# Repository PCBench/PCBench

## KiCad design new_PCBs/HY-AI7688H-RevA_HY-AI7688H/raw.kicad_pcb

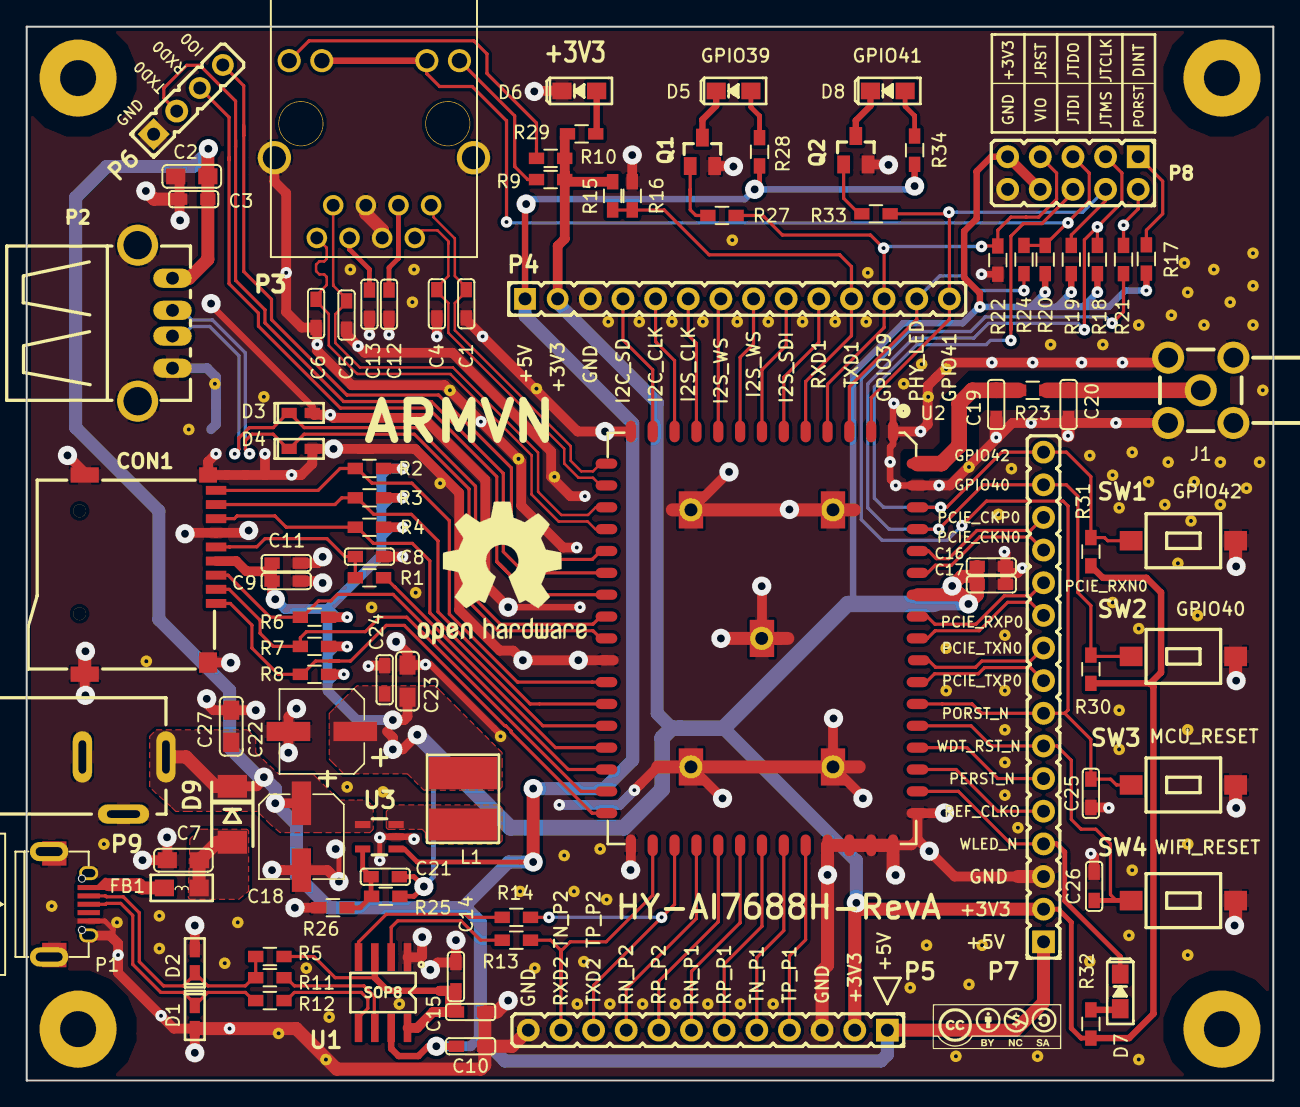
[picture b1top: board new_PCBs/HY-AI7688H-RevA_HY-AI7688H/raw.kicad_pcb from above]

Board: 2 copper layers, 97.0 x 82.0 mm, 96 parts (0 on the bottom side), 80 nets.

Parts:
C1, C4, C5, C6, C19, C20: DNP; CAPC0603x018M
C2, C7, C27: 10uF; CAPC0805X024M
C3, C10, C11, C12, C13, C14, C15, C17, C21, C24, C25, C26: 100nF; CAPC0603x018M
C8, C9: NC; CAPC0603x018M
C16: 100uF; CAPC0603x018M
C18, C22: 220uF/16V; CAPAE_6.3x7.7-M
C23: 22uF; CAPC0805X024M
CON1: TF-Micro-SDCard; TFC-WPAPR-08
D1, D2, D3, D4: TVS; DIOC_0603X018
D5, D6, D7, D8: LED; LED_0805x024M
D9: D_SS24; DO-214AA
FB1: FBM0805PT800S; FB0805x034M
J1: CONN_SMA; MOLEX_0731000114
L1: CDRH4D22; INDC5050X24M
MH1, MH2, MH3, MH4: MH_32.8MM; Mounting_hole_2.8mm
P1: USB_OTG; USB_Micro-B_DGK609-4048-1-ND
P2: USB_A; USB_A_H_PTH
P3: HR911102A
P4: CONN_01X14; HDRV14W64_1X14_3556X254X1154
P5: CONN_01X12; HDRV12W64_1X12_3048X254X1154
P6: CONN_01X04; HDRV4W64_1X4_1016X254X1154
P7: CONN_01X16; HDRV16W64_1X16_4046X254X1154
P8: CONN_02X05; HDRV10W64P254_2X5_1270X254X115P
P9: CONN-PWR-JACK; CONN_PWR_JACK_25
Q1, Q2: LMBT3904; SOT23-3-MMBT3904-M
R1, R13, R14, R21, R24: 22R; RESC0603x018M
R2, R3, R4, R6, R7, R8, R17, R30, R31: 10K; RESC0603x018M
R5: 1.5K; RESC0603x018M
R9, R10, R32: 330R; RESC0603x018M
R11, R12: 27R; RESC0603x018M
R15: 4.7K; RESC0603x018M
R16: DNP; RESC0603x018M
R18, R19, R20, R22: 1K; RESC0603x018M
R23: 0R; RESC0603x018M
R25: 47K_1%; RESC0603x018M
R26: 10.5K_1%; RESC0603x018M
R27, R33: 2.2K; RESC0603x018M
R28, R29, R34: 560R; RESC0603x018M
SW1: SW_USR1; SW-T1107A(6x3,8x2,5MM)
SW2: SW_USR2; SW-T1107A(6x3,8x2,5MM)
SW3: MPU_RESET; SW-T1107A(6x3,8x2,5MM)
SW4: WIFI_RESET; SW-T1107A(6x3,8x2,5MM)
U1: PL2303SA; SOP127P600x155-8-M
U2: AI7688H; AI7688H-M
U3: SY8008; SOT-23-5

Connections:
+3V3: C9.2, C11.2, C16.2, C17.2, C21.2, C22.1, C23.2, C24.2, CON1.4, L1.2, P4.2, P5.2, P7.2, P8.8, P8.9, R2.2, R3.2, R4.2, R6.2, R7.2, R8.2, R9.1, R10.1, R15.2, R17.2, R18.2, R19.2, R20.2, R25.2, R29.2, R30.2, R31.2, R32.1, U2.54
+5V: C2.2, C3.2, C10.2, C18.1, C27.2, D9.1, P2.1, P4.1, P5.1, P7.1, P9.1, R28.2, R34.2, U1.7, U3.1, U3.4
+5V_USBOTG: C7.2, D9.2, FB1.2
/AI7688H/D+: R12.1, U1.5
/AI7688H/D-: R11.1, U1.6
/AI7688H/EJTAG_DINT: P8.1, R17.1
/AI7688H/EJTAG_PORST_N: P8.2, R21.1
/AI7688H/EPHY_LED0_N: P3.10, P3.11, P8.5, R20.1, R24.2
/AI7688H/GPIO_0: P6.4, U2.18
/AI7688H/I2C_SCLK: P4.5, U2.11
/AI7688H/I2C_SD: P4.4, U2.12
/AI7688H/I2S_SCLK: P4.6, U2.10
/AI7688H/I2S_SDI: P4.9, U2.7
/AI7688H/I2S_SDO: P4.8, U2.8
/AI7688H/I2S_WS: P4.7, U2.9
/AI7688H/JRST_GPIO_39: P4.12, P8.7, R22.2, R27.1, U2.4
/AI7688H/JTCLK_GPIO_40: P7.15, P8.3, R18.1, R30.1, SW2.1, U2.57
/AI7688H/JTDI_GPIO_42: P7.16, P8.6, R31.1, SW1.1, U2.58
/AI7688H/JTDO_EPHY_LED0_N: P4.13, R24.1, U2.3
/AI7688H/JTMS_GPIO_41: P4.14, P8.4, R19.1, R33.1, U2.2
/AI7688H/MDI_P0_R_N: C4.2, P3.2, U2.15
/AI7688H/MDI_P0_R_P: C1.2, P3.1, U2.14
/AI7688H/MDI_P0_T_N: C6.2, P3.8, U2.17
/AI7688H/MDI_P0_T_P: C5.2, P3.7, U2.16
/AI7688H/MDI_RN_P1: P5.7, U2.36
/AI7688H/MDI_RN_P2: P5.9, U2.34
/AI7688H/MDI_RN_P3: CON1.7, R4.1, U2.26
/AI7688H/MDI_RN_P4: CON1.3, R6.1, U2.28
/AI7688H/MDI_RP_P1: P5.6, U2.37
/AI7688H/MDI_RP_P2: P5.8, U2.35
/AI7688H/MDI_RP_P3: CON1.8, R3.1, U2.25
/AI7688H/MDI_RP_P4: R1.1, U2.27
/AI7688H/MDI_TN_P1: P5.5, U2.38
/AI7688H/MDI_TN_P2: P5.11, R13.1, U2.32
/AI7688H/MDI_TN_P3: CON1.9, R2.1, U2.24
/AI7688H/MDI_TN_P4: CON1.1, R8.1, U2.30
/AI7688H/MDI_TP_P1: P5.4, U2.39
/AI7688H/MDI_TP_P2: P5.10, R14.1, U2.33
/AI7688H/MDI_TP_P4: CON1.2, R7.1, U2.29
/AI7688H/PCIE_CK0_N: P7.13, U2.55
/AI7688H/PCIE_CK0_P: P7.14, U2.56
/AI7688H/PCIE_RX0_N: P7.12, U2.53
/AI7688H/PCIE_RX0_P: P7.11, U2.52
/AI7688H/PCIE_TX0_N: P7.10, U2.51
/AI7688H/PCIE_TX0_P: P7.9, U2.50
/AI7688H/PERST_N: P7.6, U2.47
/AI7688H/PORST_N: C25.1, P7.8, R21.2, SW3.1, U2.49
/AI7688H/REF_CLKO: P7.5, U2.46
/AI7688H/RF: C19.2, R23.2, U2.60
/AI7688H/UART_7688_RXD0: P6.3, U2.20
/AI7688H/UART_7688_RXD1: P4.10, U2.6
/AI7688H/UART_7688_TXD0: P6.2, U2.19
/AI7688H/UART_7688_TXD1: P4.11, R15.1, R16.2, U2.5
/AI7688H/USB_D_N: D4.1, P2.2, U2.22
/AI7688H/USB_D_P: D3.1, P2.3, U2.21
/AI7688H/USB_OTG_D+: D1.1, P1.3, R12.2
/AI7688H/USB_OTG_D-: D2.1, P1.2, R5.1, R11.2
/AI7688H/WDT_RST_N: C26.1, P7.7, SW4.1, U2.48
/AI7688H/WLED_N: D7.1, P7.4, U2.45
GND: C1.1, C2.1, C3.1, C4.1, C5.1, C6.1, C7.1, C8.1, C9.1, C10.1, C11.1, C12.1, C13.1, C14.1, C15.1, C16.1, C17.1, C18.2, C19.1, C20.1, C22.2, C23.1, C24.1, C25.2, C26.2, C27.1, CON1.6, CON1.10, CON1.11, CON1.12, CON1.13, D1.2, D2.2, D3.2, D4.2, D6.1, J1.2, J1.3, J1.4, J1.5, P1.5, P1.6, P2.4, P2.5, P3.4, P3.5, P3.13, P3.14, P4.3, P5.3, P5.12, P6.1, P7.3, P8.10, P9.2, P9.3, Q1.2, Q2.2, R16.1, R22.1, R26.1, SW1.2, SW2.2, SW3.2, SW4.2, U1.1, U2.1, U2.13, U2.23, U2.31, U2.40, U2.41, U2.42, U2.43, U2.44, U2.59, U2.61, U2.62, U2.63, U2.64, U2.65, U3.2
unnamed: C8.2, CON1.5, R1.2
unnamed: C12.2, P3.3
unnamed: C13.2, P3.6
unnamed: C20.2, J1.1, R23.1
unnamed: C21.1, R25.1, R26.2, U3.5
unnamed: D5.1, Q1.3
unnamed: D5.2, R28.1
unnamed: D6.2, R29.1
unnamed: D7.2, R32.2
unnamed: D8.1, Q2.3
unnamed: D8.2, R34.1
unnamed: FB1.1, P1.1
unnamed: L1.1, U3.3
unnamed: P3.9, R9.2
unnamed: P3.12, R10.2
unnamed: Q1.1, R27.2
unnamed: Q2.1, R33.2
unnamed: R13.2, U1.2
unnamed: R14.2, U1.4
VO_3V3: C14.2, C15.2, R5.2, U1.3, U1.8

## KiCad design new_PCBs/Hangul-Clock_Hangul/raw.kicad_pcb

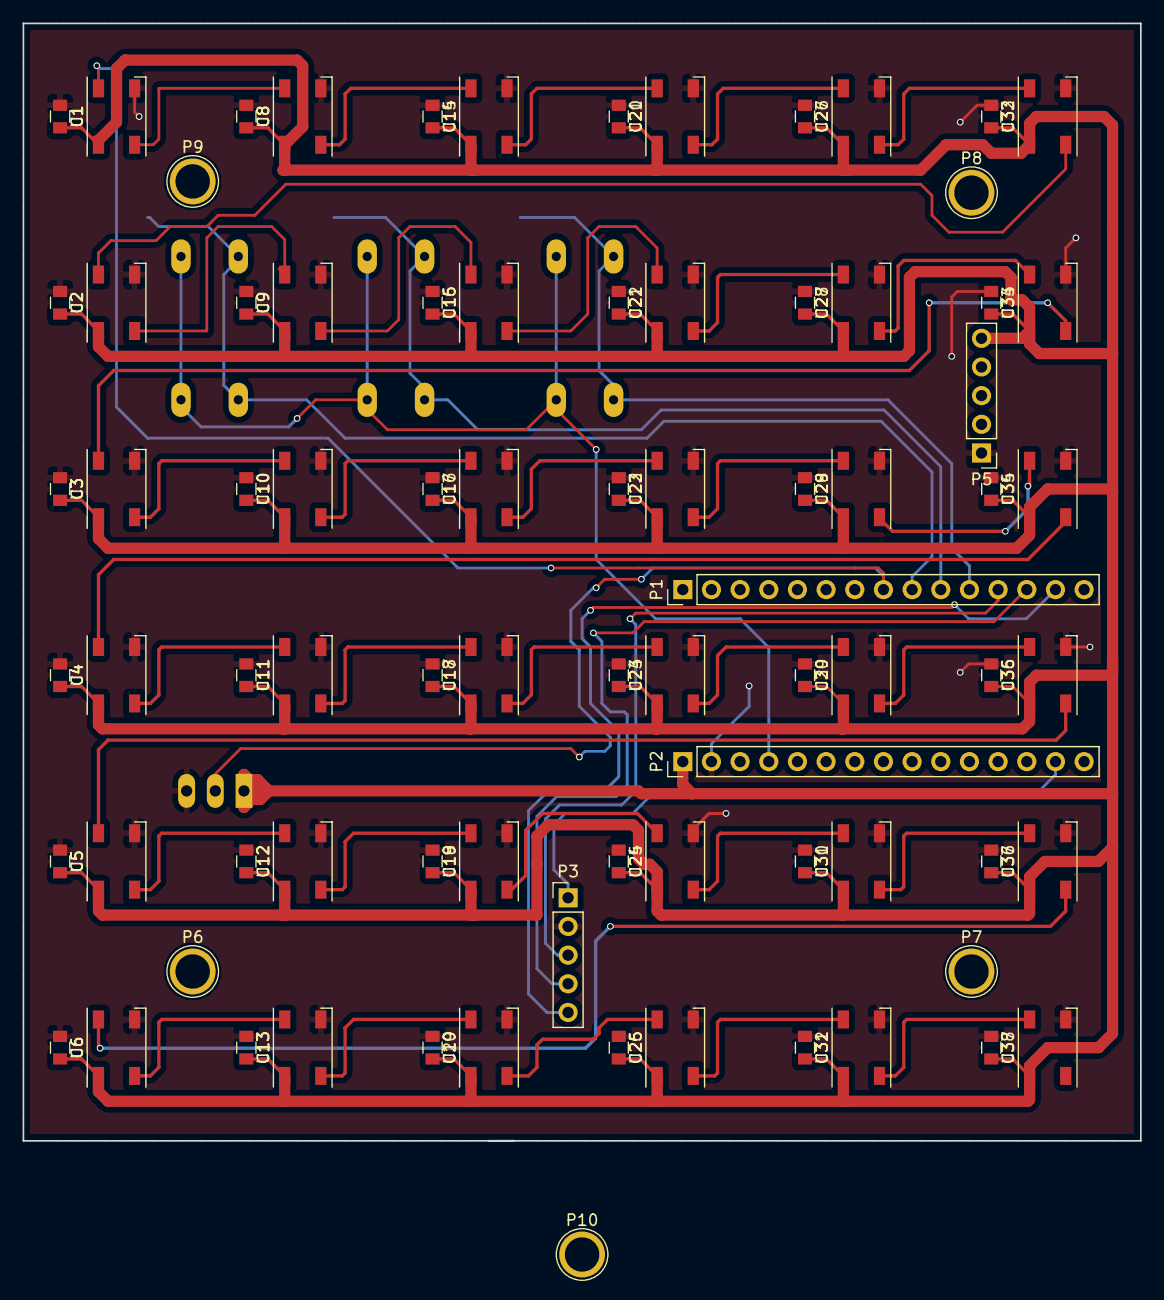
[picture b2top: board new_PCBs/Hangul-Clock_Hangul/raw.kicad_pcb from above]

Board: 2 copper layers, 99.0 x 99.0 mm, 88 parts (0 on the bottom side), 46 nets.

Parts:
C1, C2, C3, C4, C5, C6, C8, C9, C10, C11, C12, C13, C15, C16, C17, C18, C19, C20, C21, C22, C23, C24, C25, C26, C27, C28, C29, C30, C31, C32, C33, C34, C35, C36, C37, C38: C; C_0805
P1: NANO_1; Pin_Header_Straight_1x15_Pitch2.54mm
P2: NANO_2; Pin_Header_Straight_1x15_Pitch2.54mm
P3: DS1302; Pin_Header_Straight_1x05_Pitch2.54mm
P4: CONN_01X03; MOLEX-5045-03A
P5: POWER; Pin_Header_Straight_1x05_Pitch2.54mm
P6, P7, P8, P9: S; 1pin
P10: s; 1pin
R1, R2, R3: R; R_0805BCU
SW1: SW_R; SW_PUSH-12mmBCU
SW2: SW_G; SW_PUSH-12mmBCU
SW3: SW_B; SW_PUSH-12mmBCU
U1, U2, U3, U4, U5, U6, U8, U9, U10, U11, U12, U13, U14, U15, U16, U17, U18, U19, U20, U21, U22, U23, U24, U25, U26, U27, U28, U29, U30, U31, U32, U33, U34, U35, U36, U37: WS2812B; LED_WS2812B-PLCC4

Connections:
+5V: P2.4, SW1.1, SW2.1, SW3.1
+5VA: C1.2, C2.2, C3.2, C4.2, C5.2, C6.2, C8.2, C9.2, C10.2, C11.2, C12.2, C13.2, C15.2, C16.2, C17.2, C18.2, C19.2, C20.2, C21.2, C22.2, C23.2, C24.2, C25.2, C26.2, C27.2, C28.2, C29.2, C30.2, C31.2, C32.2, C33.2, C34.2, C35.2, C36.2, C37.2, C38.2, P2.1, P4.1, P5.5, U1.1, U2.1, U3.1, U4.1, U5.1, U6.1, U8.1, U9.1, U10.1, U11.1, U12.1, U13.1, U14.1, U15.1, U16.1, U17.1, U18.1, U19.1, U20.1, U21.1, U22.1, U23.1, U24.1, U25.1, U26.1, U27.1, U28.1, U29.1, U30.1, U31.1, U32.1, U33.1, U34.1, U35.1, U36.1, U37.1
CLK: P1.12, P3.3
DAT: P1.13, P3.4
DIN: P1.8, P4.2, U1.4
GND: C1.1, C2.1, C3.1, C4.1, C5.1, C6.1, C8.1, C9.1, C10.1, C11.1, C12.1, C13.1, C15.1, C16.1, C17.1, C18.1, C19.1, C20.1, C21.1, C22.1, C23.1, C24.1, C25.1, C26.1, C27.1, C28.1, C29.1, C30.1, C31.1, C32.1, C33.1, C34.1, C35.1, C36.1, C37.1, C38.1, P1.4, P2.2, P3.2, P4.3, P5.1, R1.1, R2.1, R3.1, U1.3, U2.3, U3.3, U4.3, U5.3, U6.3, U8.3, U9.3, U10.3, U11.3, U12.3, U13.3, U14.3, U15.3, U16.3, U17.3, U18.3, U19.3, U20.3, U21.3, U22.3, U23.3, U24.3, U25.3, U26.3, U27.3, U28.3, U29.3, U30.3, U31.3, U32.3, U33.3, U34.3, U35.3, U36.3, U37.3
unnamed: P1.9, R1.2, SW1.2
unnamed: P1.10, R2.2, SW2.2
unnamed: P1.11, R3.2, SW3.2
unnamed: P2.14, P3.1
unnamed: U1.2, U8.4
unnamed: U2.2, U9.4
unnamed: U2.4, U32.2
unnamed: U3.4, U33.2
unnamed: U10.2, U16.4
unnamed: U3.2, U10.4
unnamed: U11.2, U17.4
unnamed: U4.2, U11.4
unnamed: U12.2, U18.4
unnamed: U5.2, U12.4
unnamed: U13.2, U19.4
unnamed: U6.2, U13.4
unnamed: U14.2, U20.4
unnamed: U8.2, U14.4
unnamed: U15.2, U21.4
unnamed: U9.2, U15.4
unnamed: U16.2, U22.4
unnamed: U17.2, U23.4
unnamed: U18.2, U24.4
unnamed: U19.2, U25.4
unnamed: U20.2, U26.4
unnamed: U21.2, U27.4
unnamed: U22.2, U28.4
unnamed: U23.2, U29.4
unnamed: U24.2, U30.4
unnamed: U25.2, U31.4
unnamed: U26.2, U32.4
unnamed: U27.2, U33.4
unnamed: U28.2, U34.4
unnamed: U29.2, U35.4
unnamed: U30.2, U36.4
unnamed: U31.2, U37.4
unnamed: U4.4, U34.2
unnamed: U5.4, U35.2
unnamed: U6.4, U36.2
RST: P1.14, P3.5

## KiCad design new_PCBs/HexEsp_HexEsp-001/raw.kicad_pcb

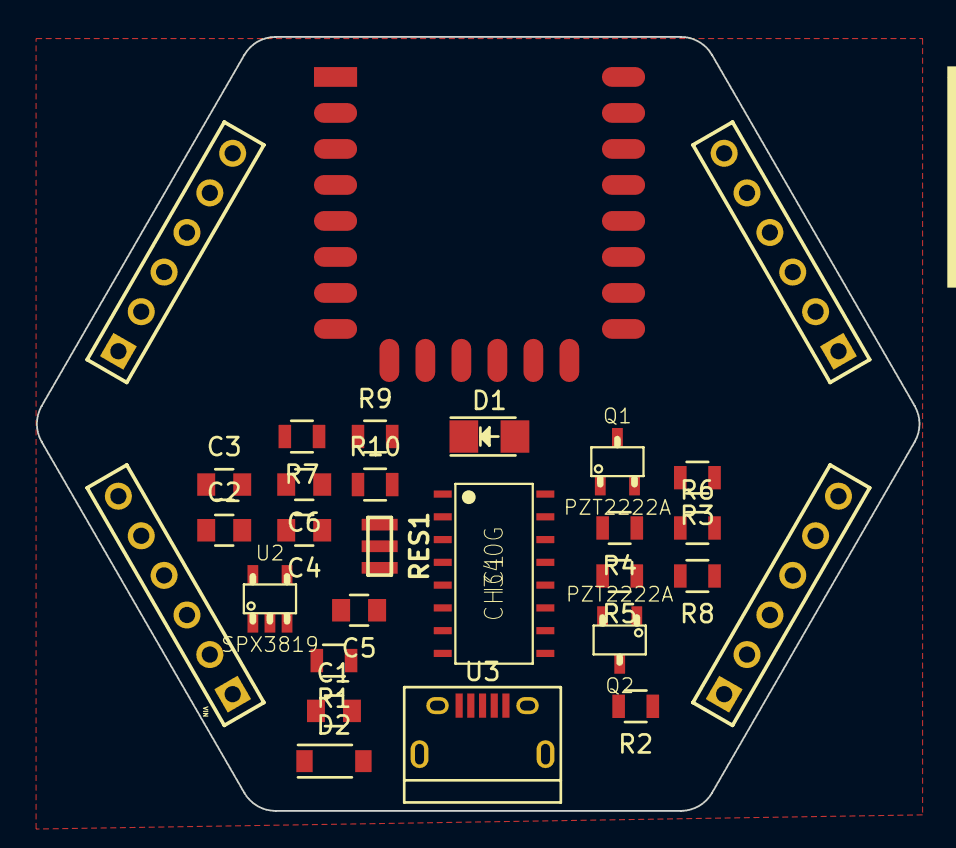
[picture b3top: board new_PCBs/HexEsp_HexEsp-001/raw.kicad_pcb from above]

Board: 2 copper layers, 49.0 x 43.0 mm, 29 parts (0 on the bottom side), 30 nets.

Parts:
C1, C2, C4: 10uF; C_0805
C3: 1uF; C_0805
C5, C6: 100nF; C_0805
D1: PURPLE; LED_1206
D2: MBR120; SOD-123
IC1: CH340G; SOP-16
J1, J2, J3, J4: 1x6_female_pin_Header_2.54mm; 1x6-Socket-header-2.54mm
Q1, Q2: PZT2222A; AB2_SOT23-3
R1, R2, R4, R5: 10K; R_0805
R3, R6, R7, R8: 1K; R_0805
R9, R10: 470; R_0805
RES1: AB2_RES_3P; murata-resonator_SMD_CSTCE8M00G55-R0
U1: ESP-12E
U2: SPX3819; AB2_SOT23-5
U3: MICRO-B_USB; USB_Micro-B

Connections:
+3V3: C2.1, C3.1, D1.2, J2.2, J4.4, R2.1, R6.2, R7.2, U1.8, U2.5
/ADC: J1.5, U1.2
/CH_PD: J1.4, R7.1, U1.3
/D+: IC1.5, U3.3
/D-: IC1.6, U3.2
/DTR: IC1.13, Q1.3, R5.2
/EN: R1.2, U2.3
/GPIO0: J3.2, Q1.2, R3.1, U1.18
/GPIO2: J3.1, R6.1, U1.17
/GPIO4: J3.3, U1.19
/GPIO5: J3.4, U1.20
/GPIO12: J2.5, U1.6
/GPIO13: J2.4, U1.7
/GPIO14: J2.6, U1.5
/GPIO15: J4.6, R8.2, U1.16
/GPIO16: J1.3, U1.4
/RESET: J1.6, Q2.2, R2.2, U1.1
/RTS: IC1.14, Q2.3, R4.2
/RXD: J3.5, R9.1, U1.21
/TXD: J3.6, R10.1, U1.22
/XI: IC1.7, RES1.1
/XO: IC1.8, RES1.3
GND: C1.2, C2.2, C3.2, C4.2, C5.2, C6.2, IC1.1, J2.3, J4.5, R8.1, RES1.2, U1.15, U2.2, U3.5
unnamed: C5.1, IC1.4
unnamed: D1.1, R3.2
unnamed: IC1.2, R9.2
unnamed: IC1.3, R10.2
unnamed: Q1.1, R4.1
unnamed: Q2.1, R5.1
VBUS: C1.1, C4.1, C6.1, D2.1, D2.2, IC1.16, J2.1, J4.1, R1.1, U2.1, U3.1

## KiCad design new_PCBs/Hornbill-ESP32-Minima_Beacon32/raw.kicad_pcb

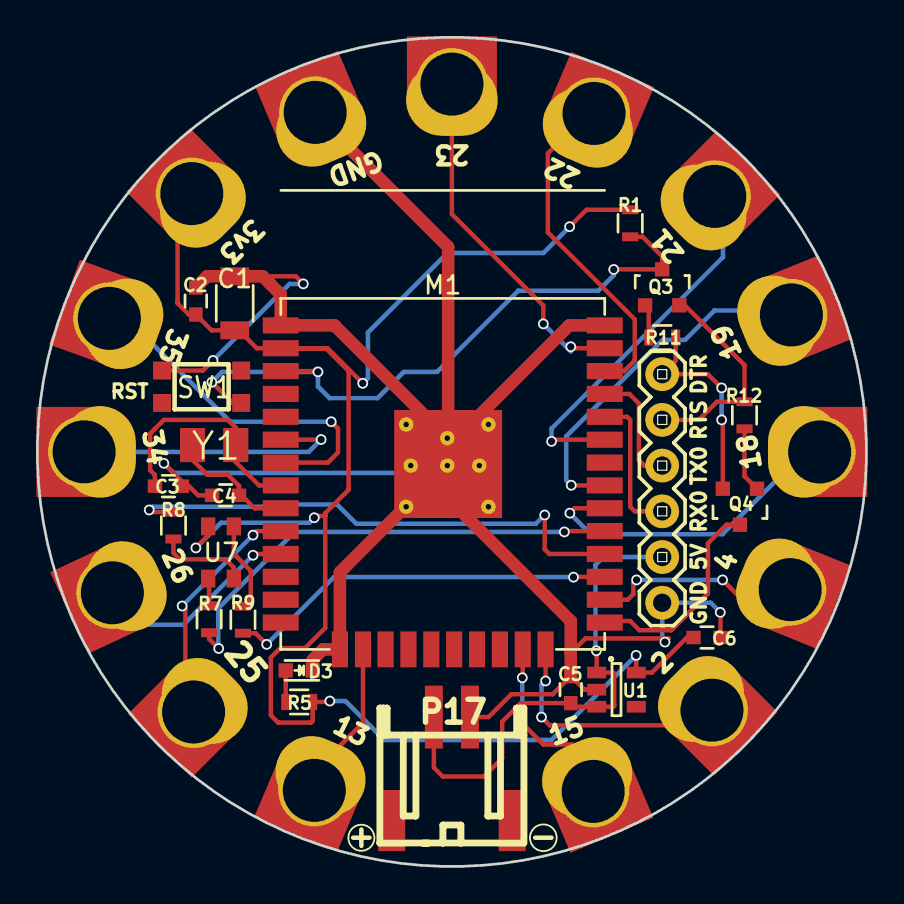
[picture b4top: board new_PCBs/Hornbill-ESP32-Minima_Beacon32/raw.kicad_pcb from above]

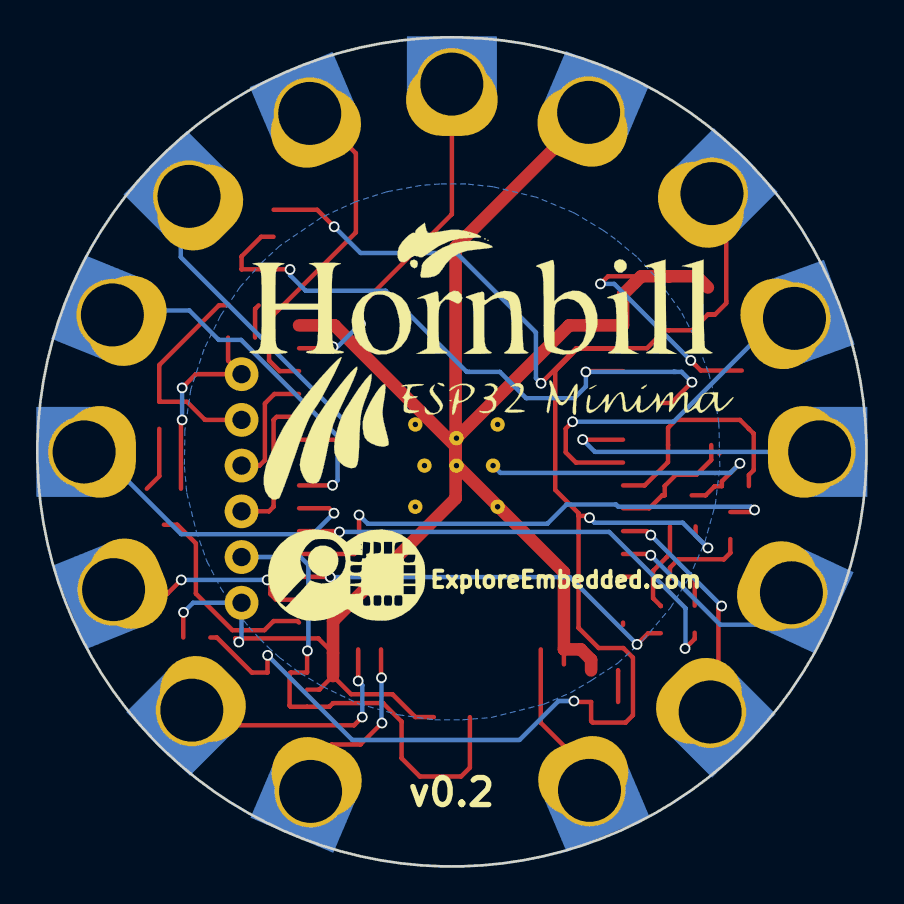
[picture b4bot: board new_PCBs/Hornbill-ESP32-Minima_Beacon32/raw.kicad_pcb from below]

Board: 2 copper layers, 46.1 x 46.1 mm, 40 parts (2 on the bottom side), 33 nets.

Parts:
C1: 100uF; C_1206
C2: 100nF; C_0603
C3, C4: 15pF; C_0603
C5: 1uF; C_0603
C6: 2.2uF; C_0603
D3: LED; LED-0603
M1: ESP-WROOM-32; ESP-32S
P1, P3, P4, P5, P6, P7, P8, P9, P10, P11, P12, P13, P14, P15, P16: CONN_01X01; MinimaPad_3.5mm
P2: CONN_01X06; 1X06
P17: CONN_01X02; s2b-ph-sm4-tb
Q3, Q4: S8050; SOT-23
R1: 10k; R_0603
R5: 1K; R_0603
R7: 150E; R_0603
R8, R9: 100E; R_0603
R11, R12: 12K; R_0603
SW1: SW_PUSH; smd_push2_New
U1: AP2112K; SOT-23-5
U2: EE_Logo; Hornbill_ESP32_minima
U3: EE_Logo; Logo_8
U7: RGB_4pin; RGB_SMD_4pin_New
Y1: 32.768KHz RTC Crystal; SMD_RTC_Crstl

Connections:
+3V3: C1.1, C2.1, C6.1, M1.2, P1.1, R1.1, R5.2, U1.5, U7.1
+5V: C5.1, P2.2, P17.1, U1.1, U1.3
/2: M1.24, P5.1
/4: M1.26, P11.1
/13: M1.16, P13.1
/15: M1.23, P12.1
/18: M1.30, P8.1
/19: M1.31, P7.1
/21: M1.33, P3.1
/22: M1.36, P4.1
/23: M1.37, P6.1
/25: M1.10, P14.1
/26: M1.11, P15.1
/34: M1.6, P9.1
/35: M1.7, P10.1
/B: M1.27, R9.1
/DTR: P2.6, Q4.2, R11.2
/EN: M1.3, Q3.3, R1.2, SW1.2
/G: M1.28, R8.1
/IO0: M1.25, Q4.3
/R: M1.29, R7.1
/RTS: P2.5, Q3.2, R12.2
/RXD0: M1.34, P2.3
/TXD0: M1.35, P2.4
GND: C1.2, C2.2, C3.2, C4.2, C5.2, C6.2, D3.1, M1.1, M1.15, M1.38, P2.1, P16.1, P17.2, SW1.1, U1.2
unnamed: C3.1, M1.8, Y1.1
unnamed: C4.1, M1.9, Y1.2
unnamed: D3.2, R5.1
unnamed: Q3.1, R11.1
unnamed: Q4.1, R12.1
unnamed: R7.2, U7.2
unnamed: R8.2, U7.4
unnamed: R9.2, U7.3

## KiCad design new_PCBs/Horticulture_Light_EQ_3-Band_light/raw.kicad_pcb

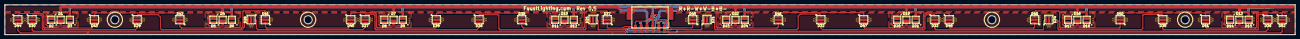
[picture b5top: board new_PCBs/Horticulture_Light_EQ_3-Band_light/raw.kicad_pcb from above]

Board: 2 copper layers, 551.2 x 12.7 mm, 53 parts (0 on the bottom side), 47 nets.

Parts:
D1, D2, D3, D4, D5, D6, D7, D8, D9, D10, D11, D12, D13, D14, D15, D16, D17, D18, D19, D20, D21, D22, D23, D24: Led_Small; MP3030
D25, D26, D27, D28, D29, D30, D31, D32, D33, D34, D35, D36: Blue 450nm; Blue_450nm
D37, D38, D39, D40, D41, D42, D43, D44, D45, D46, D47, D48, D49, D50, D51, D52: Deep Red 660nm; Deep_Red_660nm
P1: CONN_02X03; 1814676

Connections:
B+: D25.2, D31.2, P1.5
B-: D30.1, D36.1, P1.6
unnamed: D1.1, D2.2
unnamed: D2.1, D3.2
unnamed: D4.1, D5.2
unnamed: D5.1, D6.2
unnamed: D7.1, D8.2
unnamed: D8.1, D9.2
unnamed: D10.1, D11.2
unnamed: D11.1, D12.2
unnamed: D13.1, D14.2
unnamed: D14.1, D15.2
unnamed: D16.1, D17.2
unnamed: D17.1, D18.2
unnamed: D19.1, D20.2
unnamed: D20.1, D21.2
unnamed: D22.1, D23.2
unnamed: D23.1, D24.2
unnamed: D25.1, D26.2
unnamed: D26.1, D27.2
unnamed: D27.1, D28.2
unnamed: D28.1, D29.2
unnamed: D29.1, D30.2
unnamed: D31.1, D32.2
unnamed: D32.1, D33.2
unnamed: D33.1, D34.2
unnamed: D34.1, D35.2
unnamed: D35.1, D36.2
unnamed: D37.1, D38.2
unnamed: D38.1, D39.2
unnamed: D39.1, D40.2
unnamed: D40.1, D41.2
unnamed: D41.1, D42.2
unnamed: D42.1, D43.2
unnamed: D43.1, D44.2
unnamed: D45.1, D46.2
unnamed: D46.1, D47.2
unnamed: D47.1, D48.2
unnamed: D48.1, D49.2
unnamed: D49.1, D50.2
unnamed: D50.1, D51.2
unnamed: D51.1, D52.2
R+: D37.2, D45.2, P1.1
R-: D44.1, D52.1, P1.2
THERMAL: D25.3, D26.3, D27.3, D28.3, D29.3, D30.3, D31.3, D32.3, D33.3, D34.3, D35.3, D36.3, D37.3, D38.3, D39.3, D40.3, D41.3, D42.3, D43.3, D44.3, D45.3, D46.3, D47.3, D48.3, D49.3, D50.3, D51.3, D52.3
W+: D1.2, D4.2, D7.2, D10.2, D13.2, D16.2, D19.2, D22.2, P1.3
W-: D3.1, D6.1, D9.1, D12.1, D15.1, D18.1, D21.1, D24.1, P1.4

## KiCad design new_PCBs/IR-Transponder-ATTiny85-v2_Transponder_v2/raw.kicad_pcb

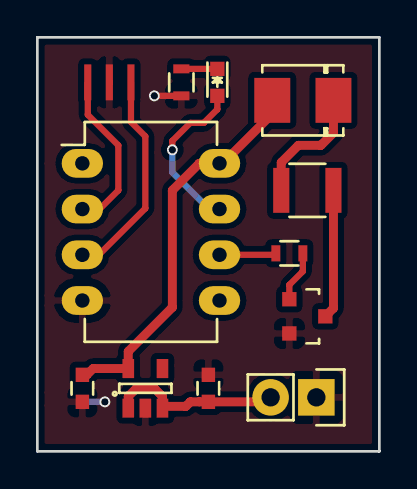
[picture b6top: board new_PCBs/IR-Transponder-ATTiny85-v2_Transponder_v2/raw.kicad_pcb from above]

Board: 2 copper layers, 19.0 x 23.0 mm, 12 parts (0 on the bottom side), 11 nets.

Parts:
C1, C2: .1u; C_0603
D1: LED; DO-214BA
D2: LED; LED_0603
IC1: ATTINY85-S; DIP-8_W7.62mm_LongPads
P1: CONN_01X02; Pin_Header_Straight_1x02
Q1: NMOS; SOT-23
R1, R3: 470; R_0603
R2: 100; R_1210
U1: 5.5v Reg; SOT-23-5
X1: CRYSTAL_SMD; myResonator

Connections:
+5V: C2.1, D1.2, IC1.8, U1.5
GND: C1.2, C2.2, IC1.4, P1.1, Q1.2, R3.2, U1.2, X1.3
unnamed: C1.1, P1.2, U1.1, U1.3
unnamed: D1.1, R2.1
unnamed: D2.1, R3.1
unnamed: IC1.2, X1.1
unnamed: IC1.3, X1.2
unnamed: Q1.1, R1.2
unnamed: Q1.3, R2.2
PB1: IC1.6, R1.1
PB2: D2.2, IC1.7

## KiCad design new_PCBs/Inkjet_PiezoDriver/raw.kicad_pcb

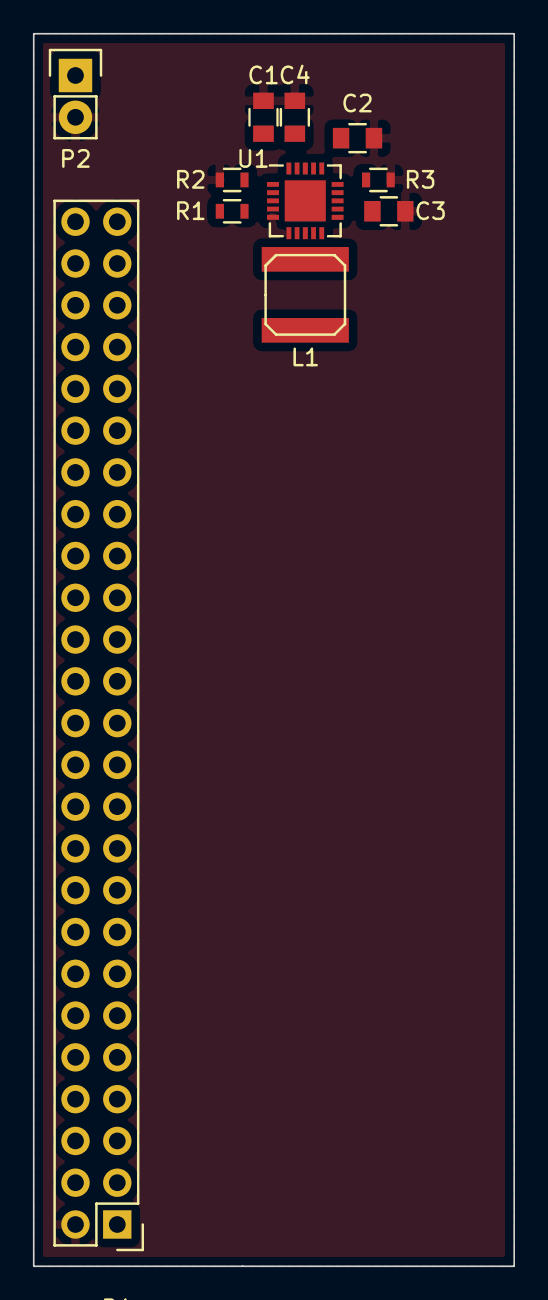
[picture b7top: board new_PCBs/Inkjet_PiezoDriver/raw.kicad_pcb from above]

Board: 2 copper layers, 29.2 x 74.9 mm, 11 parts (0 on the bottom side), 11 nets, no tracks yet.

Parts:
C1, C2, C3, C4: C; C_0805
L1: INDUCTOR; SELF-WE-TPC_M
P1: CONN_02X25; Pin_Header_Straight_2x25
P2: CONN_01X02; Pin_Header_Straight_1x02
R1, R2, R3: R; R_0603
U1: DRV8662; QFN-20-1EP_4x4mm_Pitch0.5mm

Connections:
GND: C1.2, C2.2, C3.2, C4.2, P1.2, P2.2, R2.2, R3.1, U1.4, U1.5, U1.6
unnamed: C1.1, U1.1
unnamed: C2.1, U1.16
unnamed: C3.1, U1.14
unnamed: L1.2, U1.7, U1.8
unnamed: P1.40, U1.17
unnamed: P2.1, U1.13
unnamed: R1.1, U1.10, U1.11, U1.12
unnamed: R1.2, R2.1, U1.3
unnamed: R3.2, U1.15
VDD: C4.1, L1.1, P1.3, U1.2, U1.18, U1.19, U1.20
